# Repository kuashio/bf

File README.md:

# Brainfuino [-]+.
An Arduino competitor that runs native brainfuck! I've condensed the explanation in this video: https://youtu.be/QloNq8AoHvU

Before going further, please make sure you know (or remember) what brainfuck is. [Here's Wikipedia's entry as a refresher](https://en.wikipedia.org/wiki/Brainfuck).

Also, before moving forward: This is not a joke. It ***is*** about a joke programming language, but a joke lots of nerds are very fond of. When I say nerds, I mean real geeks: Not gamers or technophiles, but geeks who like to read [The Art of Computer Programming](https://en.wikipedia.org/wiki/The_Art_of_Computer_Programming) just for kicks!

The Brainfuino [-]+. (pronounced "Brainfuino Uno") is a development board for a brainfuck soft processor I wrote in Verilog, named [***brainfuck_uP***](https://github.com/kuashio/brainfuck_uP) (as in "brainfuck microprocessor"), which runs brainfuck code natively, that is, the plain text of a brainfuck source file, yes, ascii characters.

Here are some details:

- brainfuck_uP is implemented in a Lattice MachXO2 FPGA, very much like the one in the [TinyFPGA AX2](https://www.sparkfun.com/products/14828) board, but in a TQFP100 package.
- brainfuck_uP is a *Harvard* machine, so it has two separate buses for its program and data memories. 
- The Brainfuino has a 128kB RAM chip and a 256kB chip, both with a good old parallel interface to work as the data and program memories of brainfuck_uP respectively.
- The I/O is adapted from 3.3V logic to TTL with a separate chip (to resemble the Arduino Uno).
- The host computer interface is a USB Virtual COM port implemented with an STM32F072 MCU, which overrides the input/output ports of brainfuck_uP for easy user-brainfuck interaction.
- The MCU is also donating its ADC to give Brainfuino the power of analog input. 
- The board has hardware for updating both the MCU firmware and the FPGA design.

## Advantages over the Arduino Uno

This product is intended as anything around brainfuck and esoteric programming languages: A joke. An elaborate joke. A geek toy.

So, if we take the Arduino as a competitor, here are some advantages:

- Brainfuino runs brainfuck! You'll get to learn a classic esoteric programming language.
- Brainfuino is the only brainfuck MCU platform of its kind (that I know of).
- Brainfuino is capable of at least competing with the Arduino by having an analog input channel.
- Brainfuino may serve as a teaching tool for several things: FPGA soft-processor development, computer science, esoteric programming languages, tinkering, hardware, etc.
- Lots of fun by matching the Arduino Community's codebase.
- Bragging rights for writing code that works! You certainly won't get that from the Arduino. 
- A *Guinness Record* may come out from the Brainfuino Community. Think an Operating System, or an actual home security system!

## Computer Languages

There are three computer languages involved. Only the first one is really intended for the end-user:

- **brainfuck:** Users will write their code in brainfuck, and the Brainfuino will run it.
- **Verilog:** brainfuck_uP was written in Verilog. The final .jedec file may be written into the FPGA's internal ROM at any time.
- **C/C++:** The firmware in the STM32 MCU was written in C. This firmware can be written into the MCU at any time as well.

## Related Projects

- [brainfuck_uP](https://github.com/kuashio/brainfuck_up). The soft processor running on the Brainfuino.
- [Brainfuino MCU firmware](https://github.com/kuashio/brainfuino-firmware). The firmware running in the STM32F072 MCU.

- [Visual brainfuck](https://sites.google.com/site/visualbf/). A brainfuck IDE I finished back in 2011.

## Contact

Eduardo Corpeño

For bug report or anything related to Brainfuino, I may be reached at kuashio@gmail.com

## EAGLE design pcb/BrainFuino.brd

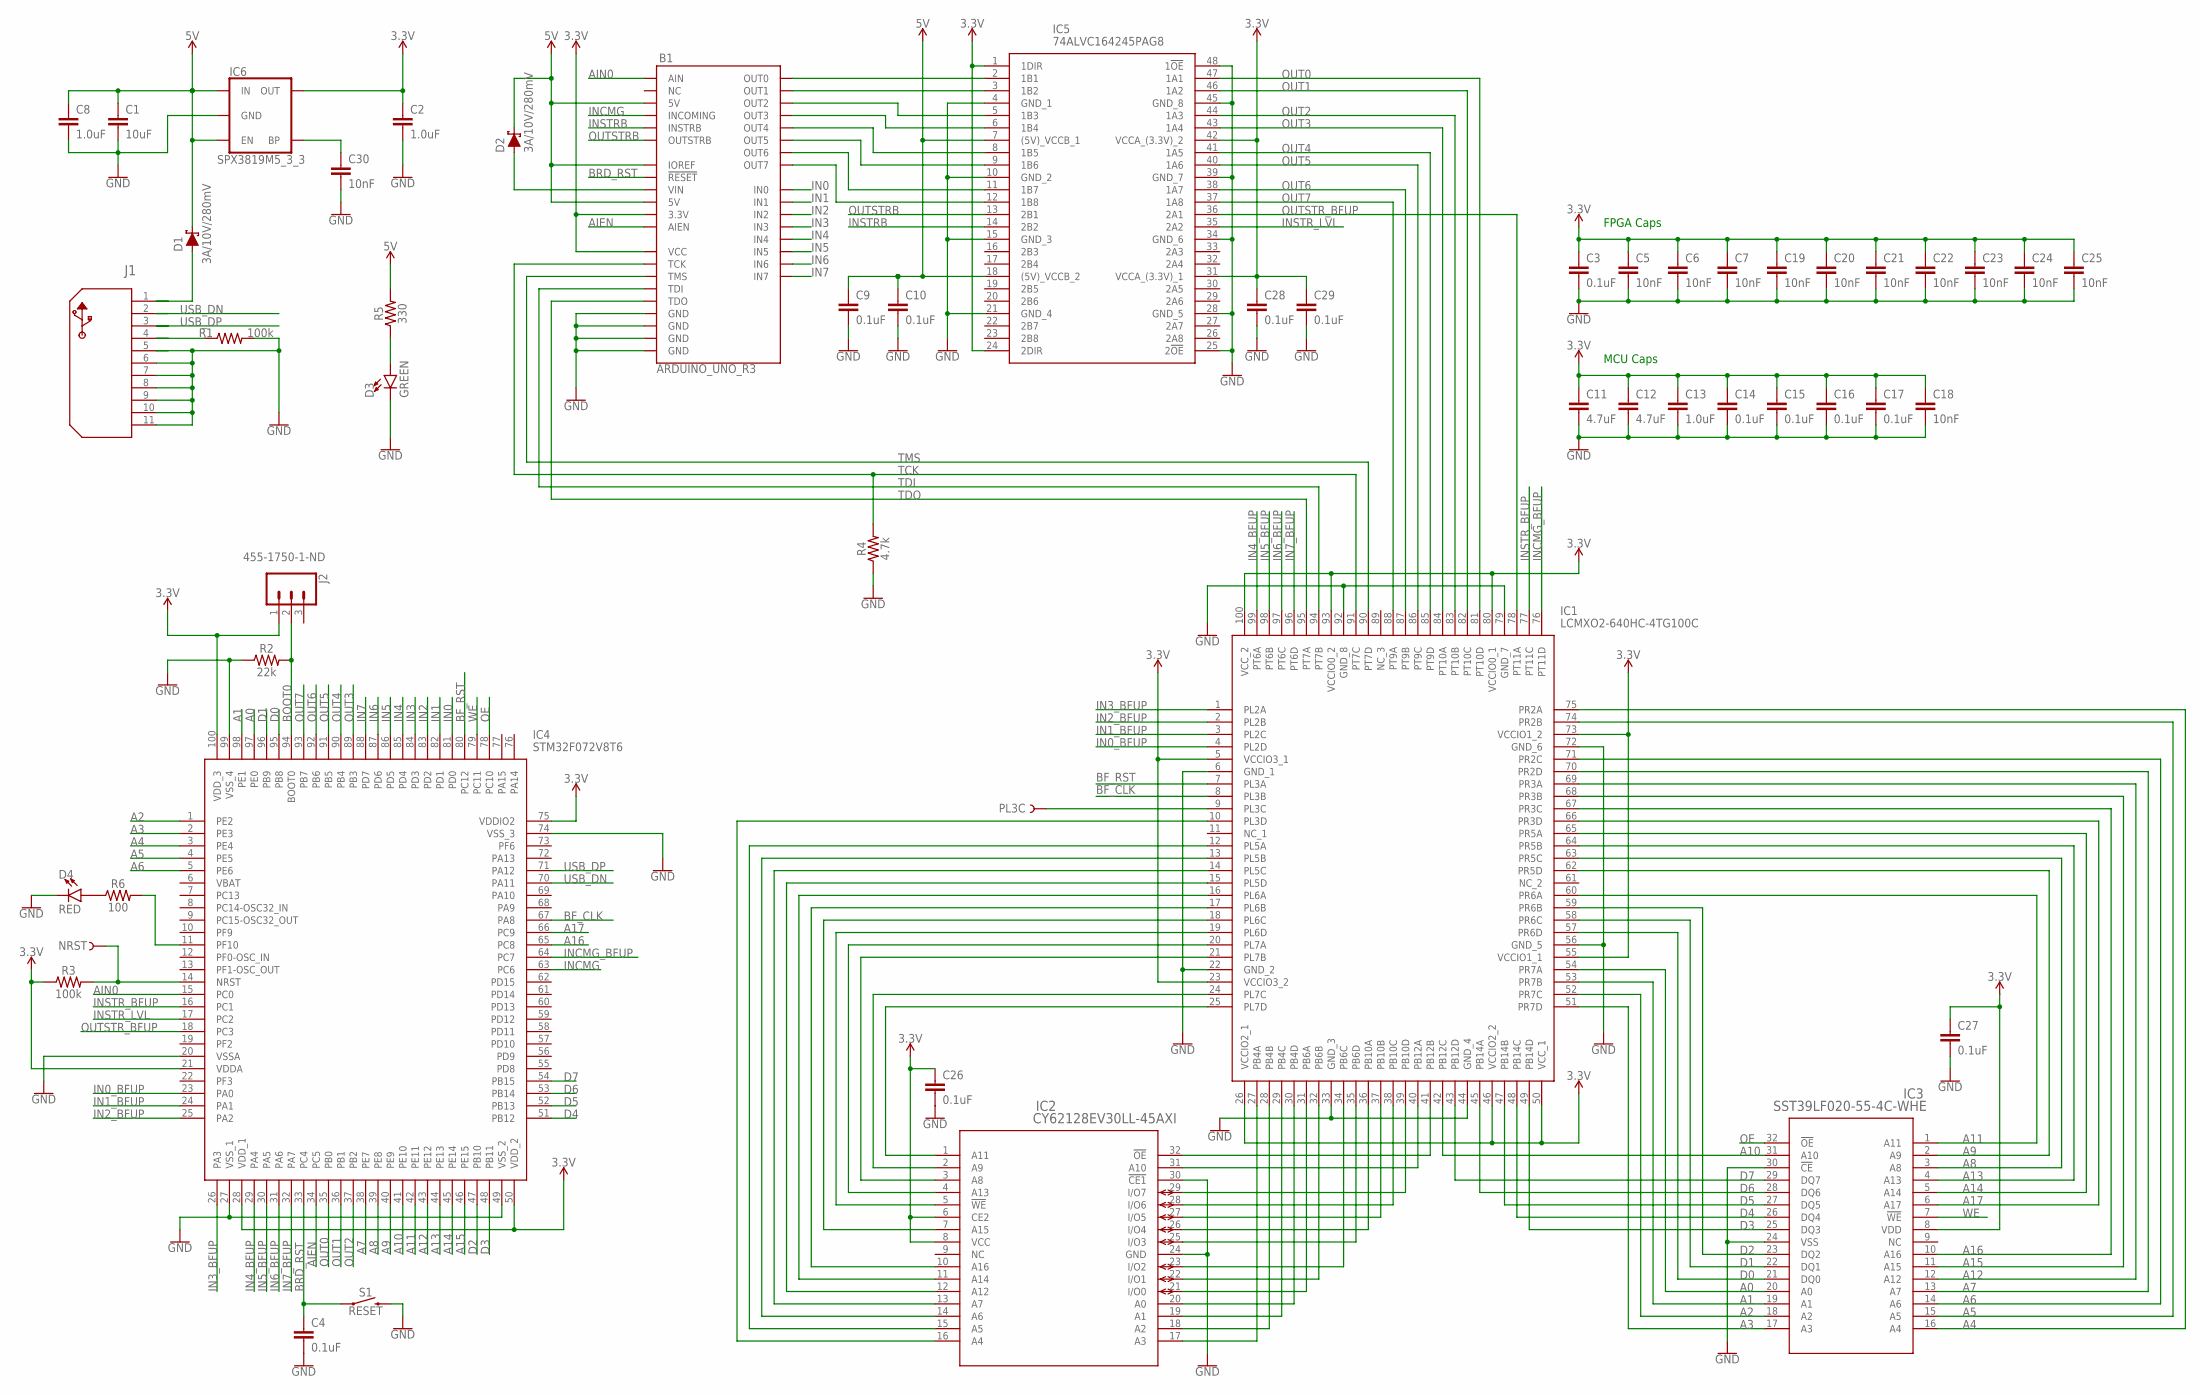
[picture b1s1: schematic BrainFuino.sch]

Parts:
B1: ARDUINO_UNO_R3; ARDUINO_R3
C1: 10uF; 0603
C2, C8, C13: 1.0uF; 0603
C3, C4, C9, C10, C14, C15, C16, C17, C26, C27, C28, C29: 0.1uF; 0603
C5, C6, C7, C18, C19, C20, C21, C22, C23, C24, C25, C30: 10nF; 0603
C11, C12: 4.7uF; 0603
D1, D2: 3A/10V/280mV; SOD-323
D3: GREEN; LED-0603
D4: RED; LED-0603
IC1: LCMXO2-640HC-4TG100C; QFP50P1600X1600X160-100N
IC2: CY62128EV30LL-45AXI; TSOP-32
IC3: SST39LF020-55-4C-WHE; TSOP32_WH_SST
IC4: STM32F072V8T6; QFP50P1600X1600X160-100N
IC5: 74ALVC164245PAG8; SOP50P810X120-48N
IC6: SPX3819M5_3_3; SOT23-5
J1: 1981568-1; CONN5_1981568-1_TEC
J2: 455-1750-1-ND; 1X03
NRST: TEST-POINTPOGO_PTH; 1X01_NO_SILK
PL3C: TEST-POINTPOGO_PTH; 1X01_NO_SILK
R1, R3: 100k; 0603
R2: 22k; 0603
R4: 4.7k; 0603
R5: 330; 0603
R6: 100; 0603
S1: RESET; TACTILE_SWITCH_SMD_6.2MM_TALL

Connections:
3.3V: B1.3.3V, B1.VCC, C2.1, C3.1, C5.1, C6.1, C7.1, C11.1, C12.1, C13.1, C14.1, C15.1, C16.1, C17.1, C18.1, C19.1, C20.1, C21.1, C22.1, C23.1, C24.1, C25.1, C26.1, C27.1, C28.1, C29.1, IC1.5 (VCCIO3_1), IC1.23 (VCCIO3_2), IC1.26 (VCCIO2_1), IC1.46 (VCCIO2_2), IC1.50 (VCC_1), IC1.55 (VCCIO1_1), IC1.73 (VCCIO1_2), IC1.80 (VCCIO0_1), IC1.93 (VCCIO0_2), IC1.100 (VCC_2), IC2.6 (CE2), IC2.8 (VCC), IC3.8 (VDD), IC4.21 (VDDA), IC4.28 (VDD_1), IC4.50 (VDD_2), IC4.75 (VDDIO2), IC4.100 (VDD_3), IC5.1 (1DIR), IC5.24 (2DIR), IC5.31 (VCCA_(3.3V)_1), IC5.42 (VCCA_(3.3V)_2), IC6.5 (OUT), J2.1, R3.1
5V: B1.5V, B1.5V@1 (5V), B1.IOREF, C1.1, C8.1, C9.1, C10.1, D1.C, D2.C, IC5.7 ((5V)_VCCB_1), IC5.18 ((5V)_VCCB_2), IC6.1 (IN), IC6.3 (EN), R5.2
A0: IC1.54 (PR7A), IC3.20 (A0), IC4.97 (PE0)
A1: IC1.53 (PR7B), IC3.19 (A1), IC4.98 (PE1)
A2: IC1.52 (PR7C), IC3.18 (A2), IC4.1 (PE2)
A3: IC1.51 (PR7D), IC3.17 (A3), IC4.2 (PE3)
A4: IC1.75 (PR2A), IC3.16 (A4), IC4.3 (PE4)
A5: IC1.74 (PR2B), IC3.15 (A5), IC4.4 (PE5)
A6: IC1.71 (PR2C), IC3.14 (A6), IC4.5 (PE6)
A7: IC1.70 (PR2D), IC3.13 (A7), IC4.38 (PE7)
A8: IC1.63 (PR5C), IC3.3 (A8), IC4.39 (PE8)
A9: IC1.62 (PR5D), IC3.2 (A9), IC4.40 (PE9)
A10: IC1.42 (PB12C), IC3.31 (A10), IC4.41 (PE10)
A11: IC1.60 (PR6A), IC3.1 (A11), IC4.42 (PE11)
A12: IC1.69 (PR3A), IC3.12 (A12), IC4.43 (PE12)
A13: IC1.64 (PR5B), IC3.4 (A13), IC4.44 (PE13)
A14: IC1.65 (PR5A), IC3.5 (A14), IC4.45 (PE14)
A15: IC1.68 (PR3B), IC3.11 (A15), IC4.46 (PE15)
A16: IC1.67 (PR3C), IC3.10 (A16), IC4.65 (PC8)
A17: IC1.66 (PR3D), IC3.6 (A17), IC4.66 (PC9)
AIEN: B1.AREF (AIEN), IC4.34 (PC5)
AIN0: B1.AIN, IC4.15 (PC0)
BF_CLK: IC1.8 (PL3B), IC4.67 (PA8)
BF_RST: IC1.7 (PL3A), IC4.80 (PC12)
BOOT0: IC4.94 (BOOT0), J2.2, R2.2
BRD_RST: B1.RESET@1 (!RESET!), C4.1, IC4.33 (PC4), S1.A2 (1)
D0: IC1.57 (PR6D), IC3.21 (DQ0), IC4.95 (PB8)
D1: IC1.58 (PR6C), IC3.22 (DQ1), IC4.96 (PB9)
D2: IC1.59 (PR6B), IC3.23 (DQ2), IC4.47 (PB10)
D3: IC1.49 (PB14D), IC3.25 (DQ3), IC4.48 (PB11)
D4: IC1.48 (PB14C), IC3.26 (DQ4), IC4.51 (PB12)
D5: IC1.47 (PB14B), IC3.27 (DQ5), IC4.52 (PB13)
D6: IC1.45 (PB14A), IC3.28 (DQ6), IC4.53 (PB14)
D7: IC1.43 (PB12D), IC3.29 (DQ7), IC4.54 (PB15)
GND: B1.GND@1 (GND), B1.GND@2 (GND), B1.GND@3 (GND), B1.GND@4 (GND), C1.2, C2.2, C3.2, C4.2, C5.2, C6.2, C7.2, C8.2, C9.2, C10.2, C11.2, C12.2, C13.2, C14.2, C15.2, C16.2, C17.2, C18.2, C19.2, C20.2, C21.2, C22.2, C23.2, C24.2, C25.2, C26.2, C27.2, C28.2, C29.2, C30.2, D3.C, D4.C, IC1.6 (GND_1), IC1.22 (GND_2), IC1.33 (GND_3), IC1.44 (GND_4), IC1.56 (GND_5), IC1.72 (GND_6), IC1.79 (GND_7), IC1.92 (GND_8), IC2.24 (GND), IC2.30 (!CE1), IC3.24 (VSS), IC3.30 (!CE), IC4.20 (VSSA), IC4.27 (VSS_1), IC4.49 (VSS_2), IC4.74 (VSS_3), IC4.99 (VSS_4), IC5.4 (GND_1), IC5.10 (GND_2), IC5.15 (GND_3), IC5.21 (GND_4), IC5.25 (2!OE), IC5.28 (GND_5), IC5.34 (GND_6), IC5.39 (GND_7), IC5.45 (GND_8), IC5.48 (1!OE), IC6.2 (GND), J1.5, J1.6, J1.7, J1.8, J1.9, J1.10, J1.11, R1.2, R2.1, R4.1, S1.B2 (2)
IN0: B1.IN0, IC4.81 (PD0)
IN0_BFUP: IC1.4 (PL2D), IC4.23 (PA0)
IN1: B1.IN1, IC4.82 (PD1)
IN1_BFUP: IC1.3 (PL2C), IC4.24 (PA1)
IN2: B1.IN2, IC4.83 (PD2)
IN2_BFUP: IC1.2 (PL2B), IC4.25 (PA2)
IN3: B1.IN3, IC4.84 (PD3)
IN3_BFUP: IC1.1 (PL2A), IC4.26 (PA3)
IN4: B1.IN4, IC4.85 (PD4)
IN4_BFUP: IC1.99 (PT6A), IC4.29 (PA4)
IN5: B1.IN5, IC4.86 (PD5)
IN5_BFUP: IC1.98 (PT6B), IC4.30 (PA5)
IN6: B1.IN6, IC4.87 (PD6)
IN6_BFUP: IC1.97 (PT6C), IC4.31 (PA6)
IN7: B1.IN7, IC4.88 (PD7)
IN7_BFUP: IC1.96 (PT6D), IC4.32 (PA7)
INCMG: B1.INCOMING, IC4.63 (PC6)
INCMG_BFUP: IC1.76 (PT11D), IC4.64 (PC7)
INSTRB: B1.INST (INSTRB), IC5.14 (2B2)
INSTR_BFUP: IC1.77 (PT11C), IC4.16 (PC1)
INSTR_LVL: IC4.17 (PC2), IC5.35 (2A2)
unnamed: IC1.28 (PB4B), IC2.18 (A2)
unnamed: IC1.29 (PB4C), IC2.19 (A1)
unnamed: IC1.30 (PB4D), IC2.20 (A0)
unnamed: IC1.31 (PB6A), IC2.21 (I/O0)
unnamed: IC1.32 (PB6B), IC2.22 (I/O1)
unnamed: IC1.34 (PB6C), IC2.23 (I/O2)
unnamed: IC1.35 (PB6D), IC2.25 (I/O3)
unnamed: IC1.41 (PB12B), IC2.32 (!OE)
unnamed: IC1.27 (PB4A), IC2.17 (A3)
unnamed: IC1.36 (PB10A), IC2.26 (I/O4)
unnamed: IC1.37 (PB10B), IC2.27 (I/O5)
unnamed: IC1.38 (PB10C), IC2.28 (I/O6)
unnamed: IC1.39 (PB10D), IC2.29 (I/O7)
unnamed: IC1.40 (PB12A), IC2.31 (A10)
unnamed: IC1.9 (PL3C), PL3C.1
unnamed: D3.A, R5.1
unnamed: C30.1, IC6.4 (BP)
unnamed: B1.VIN, D2.A
unnamed: D1.A, J1.1
unnamed: IC4.11 (PF10), R6.2
unnamed: D4.A, R6.1
unnamed: IC4.14 (NRST), NRST.1, R3.2
unnamed: B1.OUT0, IC5.2 (1B1)
unnamed: IC1.25 (PL7D), IC2.1 (A11)
unnamed: IC1.24 (PL7C), IC2.2 (A9)
unnamed: IC1.21 (PL7B), IC2.3 (A8)
unnamed: IC1.18 (PL6C), IC2.7 (A15)
unnamed: IC1.15 (PL5D), IC2.12 (A12)
unnamed: IC1.14 (PL5C), IC2.13 (A7)
unnamed: IC1.13 (PL5B), IC2.14 (A6)
unnamed: IC1.12 (PL5A), IC2.15 (A5)
unnamed: IC1.10 (PL3D), IC2.16 (A4)
unnamed: B1.OUT1, IC5.3 (1B2)
unnamed: B1.OUT2, IC5.5 (1B3)
unnamed: B1.OUT3, IC5.6 (1B4)
unnamed: B1.OUT4, IC5.8 (1B5)
unnamed: B1.OUT5, IC5.9 (1B6)
unnamed: IC1.17 (PL6B), IC2.10 (A16)
unnamed: B1.OUT6, IC5.11 (1B7)
unnamed: B1.OUT7, IC5.12 (1B8)
unnamed: IC1.20 (PL7A), IC2.4 (A13)
unnamed: IC1.19 (PL6D), IC2.5 (!WE)
unnamed: IC1.16 (PL6A), IC2.11 (A14)
unnamed: J1.4, R1.1
OE: IC3.32 (!OE), IC4.78 (PC10)
OUT0: IC1.81 (PT10D), IC4.35 (PB0), IC5.47 (1A1)
OUT1: IC1.82 (PT10C), IC4.36 (PB1), IC5.46 (1A2)
OUT2: IC1.83 (PT10B), IC4.37 (PB2), IC5.44 (1A3)
OUT3: IC1.84 (PT10A), IC4.89 (PB3), IC5.43 (1A4)
OUT4: IC1.85 (PT9D), IC4.90 (PB4), IC5.41 (1A5)
OUT5: IC1.86 (PT9C), IC4.91 (PB5), IC5.40 (1A6)
OUT6: IC1.87 (PT9B), IC4.92 (PB6), IC5.38 (1A7)
OUT7: IC1.88 (PT9A), IC4.93 (PB7), IC5.37 (1A8)
OUTSTRB: B1.OUTST (OUTSTRB), IC5.13 (2B1)
OUTSTR_BFUP: IC1.78 (PT11A), IC4.18 (PC3), IC5.36 (2A1)
TCK: B1.TCK, IC1.91 (PT7C), R4.2
TDI: B1.TDI, IC1.94 (PT7B)
TDO: B1.TDO, IC1.95 (PT7A)
TMS: B1.TMS, IC1.90 (PT7D)
USB_DN: IC4.70 (PA11), J1.2
USB_DP: IC4.71 (PA12), J1.3
WE: IC3.7 (!WE), IC4.79 (PC11)

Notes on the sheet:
FPGA Caps
MCU Caps

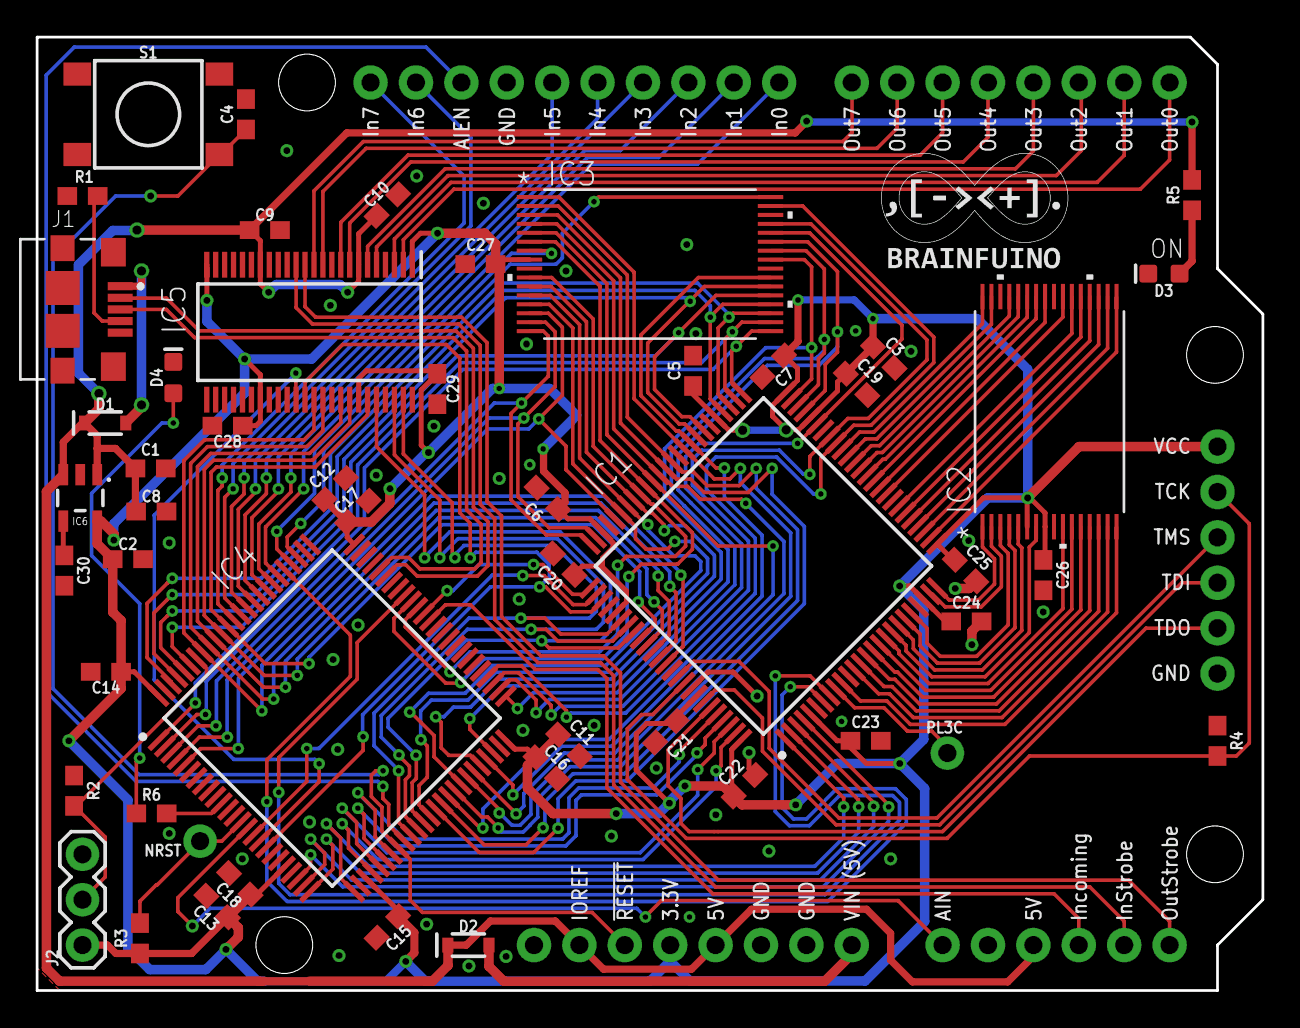
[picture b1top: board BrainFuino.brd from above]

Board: 2 copper layers, 68.6 x 53.3 mm, 52 parts (0 on the bottom side), 118 nets.

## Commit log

2021-01-04 added pcb folder
2021-01-04 updated docs
2021-01-07 readme
2021-01-07 minor changes to readme
2021-10-07 added schematic pdf

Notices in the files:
parts and their libraries:
SparkFun-Connectors: Licensing: Creative Commons ShareAlike 4.0 International - https://creativecommons.org/licenses/by-sa/4.0
COPYRIGHT: Copyright (C) 2018 Accelerated Designs. All rights reserved
COPYRIGHT: Copyright (C) 2016 Accelerated Designs. All rights reserved
